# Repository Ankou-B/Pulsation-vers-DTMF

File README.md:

## 🇫🇷 Français

# Pulsation vers DTMF

Ce projet a pour but de faire revivre de vieux téléphones à cadran en leur permettant de composer des numéros à nouveau, malgré l'arrêt des lignes analogiques. 

## 🇺🇸🇬🇧 English

# Pulse to DTMF

This project aims to bring old rotary phones back to life by allowing them to dial numbers again, despite the shutdown of analog lines.

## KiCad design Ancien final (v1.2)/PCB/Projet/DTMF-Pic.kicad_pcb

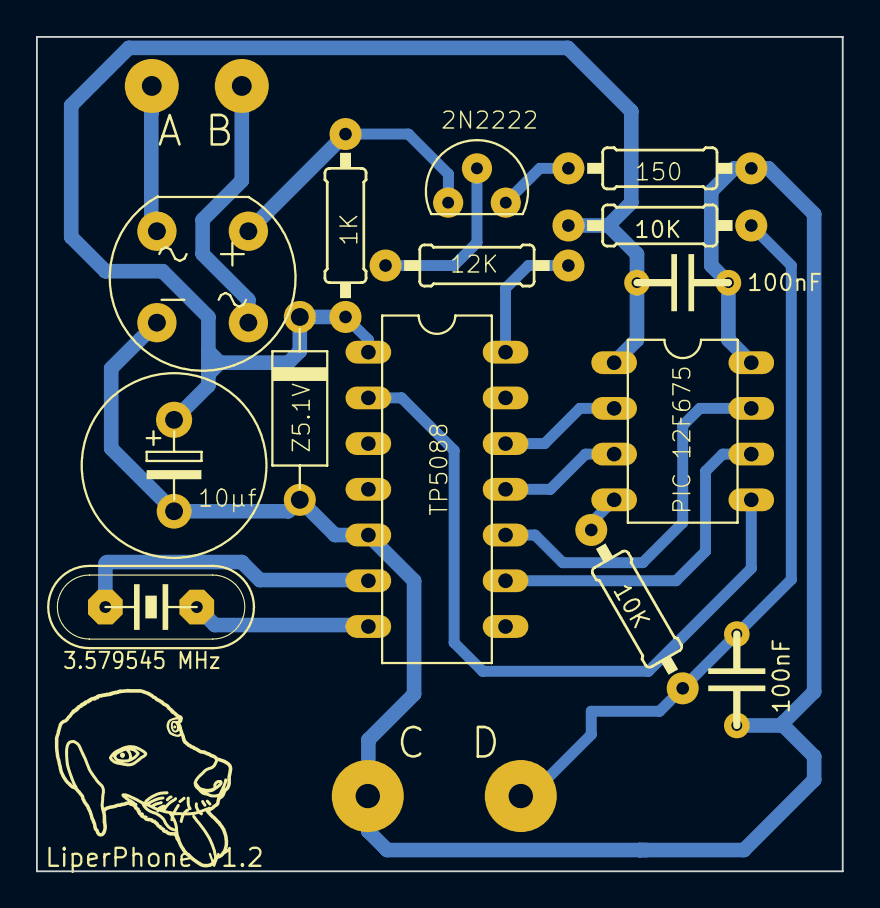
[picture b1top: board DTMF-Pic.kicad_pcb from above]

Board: 2 copper layers, 44.8 x 46.4 mm, 14 parts (0 on the bottom side), 14 nets.

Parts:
E$1: DIL-8
E$2: DIL-14
E$3: PONT1A
E$4, E$5, E$6: RES-4
E$7, E$10: 10K; RES-4
E$8: DIO-4
E$9: QUARTZ
E$11: TO-92
E$12: 0.1F; CAP-2
E$13: CHIX2-4
E$14: 0.1µf; CAP-2

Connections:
S$1: E$2.7, E$9.1
S$4: E$7.1, E$10.1
S$5: E$2.6, E$9.2
S$6: E$1.1, E$2.1, E$4.1, E$8.2, E$10.2, E$12.P$1, E$13.1
S$7: E$6.2, E$11.2
S$8: E$1.2, E$2.12
S$9: E$1.5, E$2.2
S$10: E$2.14, E$6.1
S$11: E$1.3, E$2.11
S$12: E$1.7, E$2.10
S$13: E$1.6, E$2.9
S$15: E$1.4, E$7.2
S$16: E$3.1, E$4.2
S$18: E$1.8, E$2.5, E$3.4, E$5.1, E$8.1, E$12.P$2, E$13.2, E$14.P$1

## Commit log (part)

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2025-02-03 Create test
2025-02-03 ajout du fichiers source du PCB ainsi que du Gerber
2025-02-03 Create t
2025-02-03 Déplacement du fichier source
2025-02-03 Create tr
2025-02-03 Suppression de tr
2025-02-03 Ajout du code source en C
2025-02-03 Ajout du code .Hex
2025-09-02 Create et
2025-09-02 Transfer de deux ancien dossier dans Ancien pas ouf
2025-09-02 Create caca
2025-09-02 Rajout de truc mdr dossier et tout
2025-09-02 Ajout du code + du HEX dans Final ancien et actuelle
2025-09-02 Plein de truc
2025-09-02 truc
2025-09-02 azeaz
2025-09-02 ('yf
2025-09-02 fini
2025-09-11 Cmieu lol
